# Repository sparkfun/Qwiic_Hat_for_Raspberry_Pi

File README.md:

SparkFun Qwiic pHAT v2.0 for Raspberry Pi
========================================

[*SparkFun Qwiic pHAT for Raspberry Pi*](https://www.sparkfun.com/products/15945)

This is a board that connects the I<sup>2</sup>C bus on the Raspberry Pi to 4 Qwiic connectors.

Repository Contents
-------------------

* **/Hardware** - Eagle design files (.brd, .sch)
* **/Production** - Production panel files (.brd)

Documentation
--------------
* **[Hookup Guide](https://learn.sparkfun.com/tutorials/qwiic-phat-for-raspberry-pi-hookup-guide)** - Basic hookup guide for the SparkFun Qwiic pHAT for Raspberry Pi.

Product Versions
----------------
* [DEV-15945](https://www.sparkfun.com/products/15945)- Qwiic pHAT v2.0
* [DEV-15351](https://www.sparkfun.com/products/15351)- Qwiic pHAT v1.0
* [DEV-14459](https://www.sparkfun.com/products/14459) - Qwiic HAT SparkFun Reds Initial Release
* [DEV-14292](https://www.sparkfun.com/products/14292) - SparkX Version

License Information
-------------------

This product is _**open source**_! 

Please review the LICENSE.md file for license information. 

If you have any questions or concerns on licensing, please contact technical support on our [SparkFun forums](https://forum.sparkfun.com/viewforum.php?f=152).

Distributed as-is; no warranty is given.

- Your friends at SparkFun.

_<COLLABORATION CREDIT>_

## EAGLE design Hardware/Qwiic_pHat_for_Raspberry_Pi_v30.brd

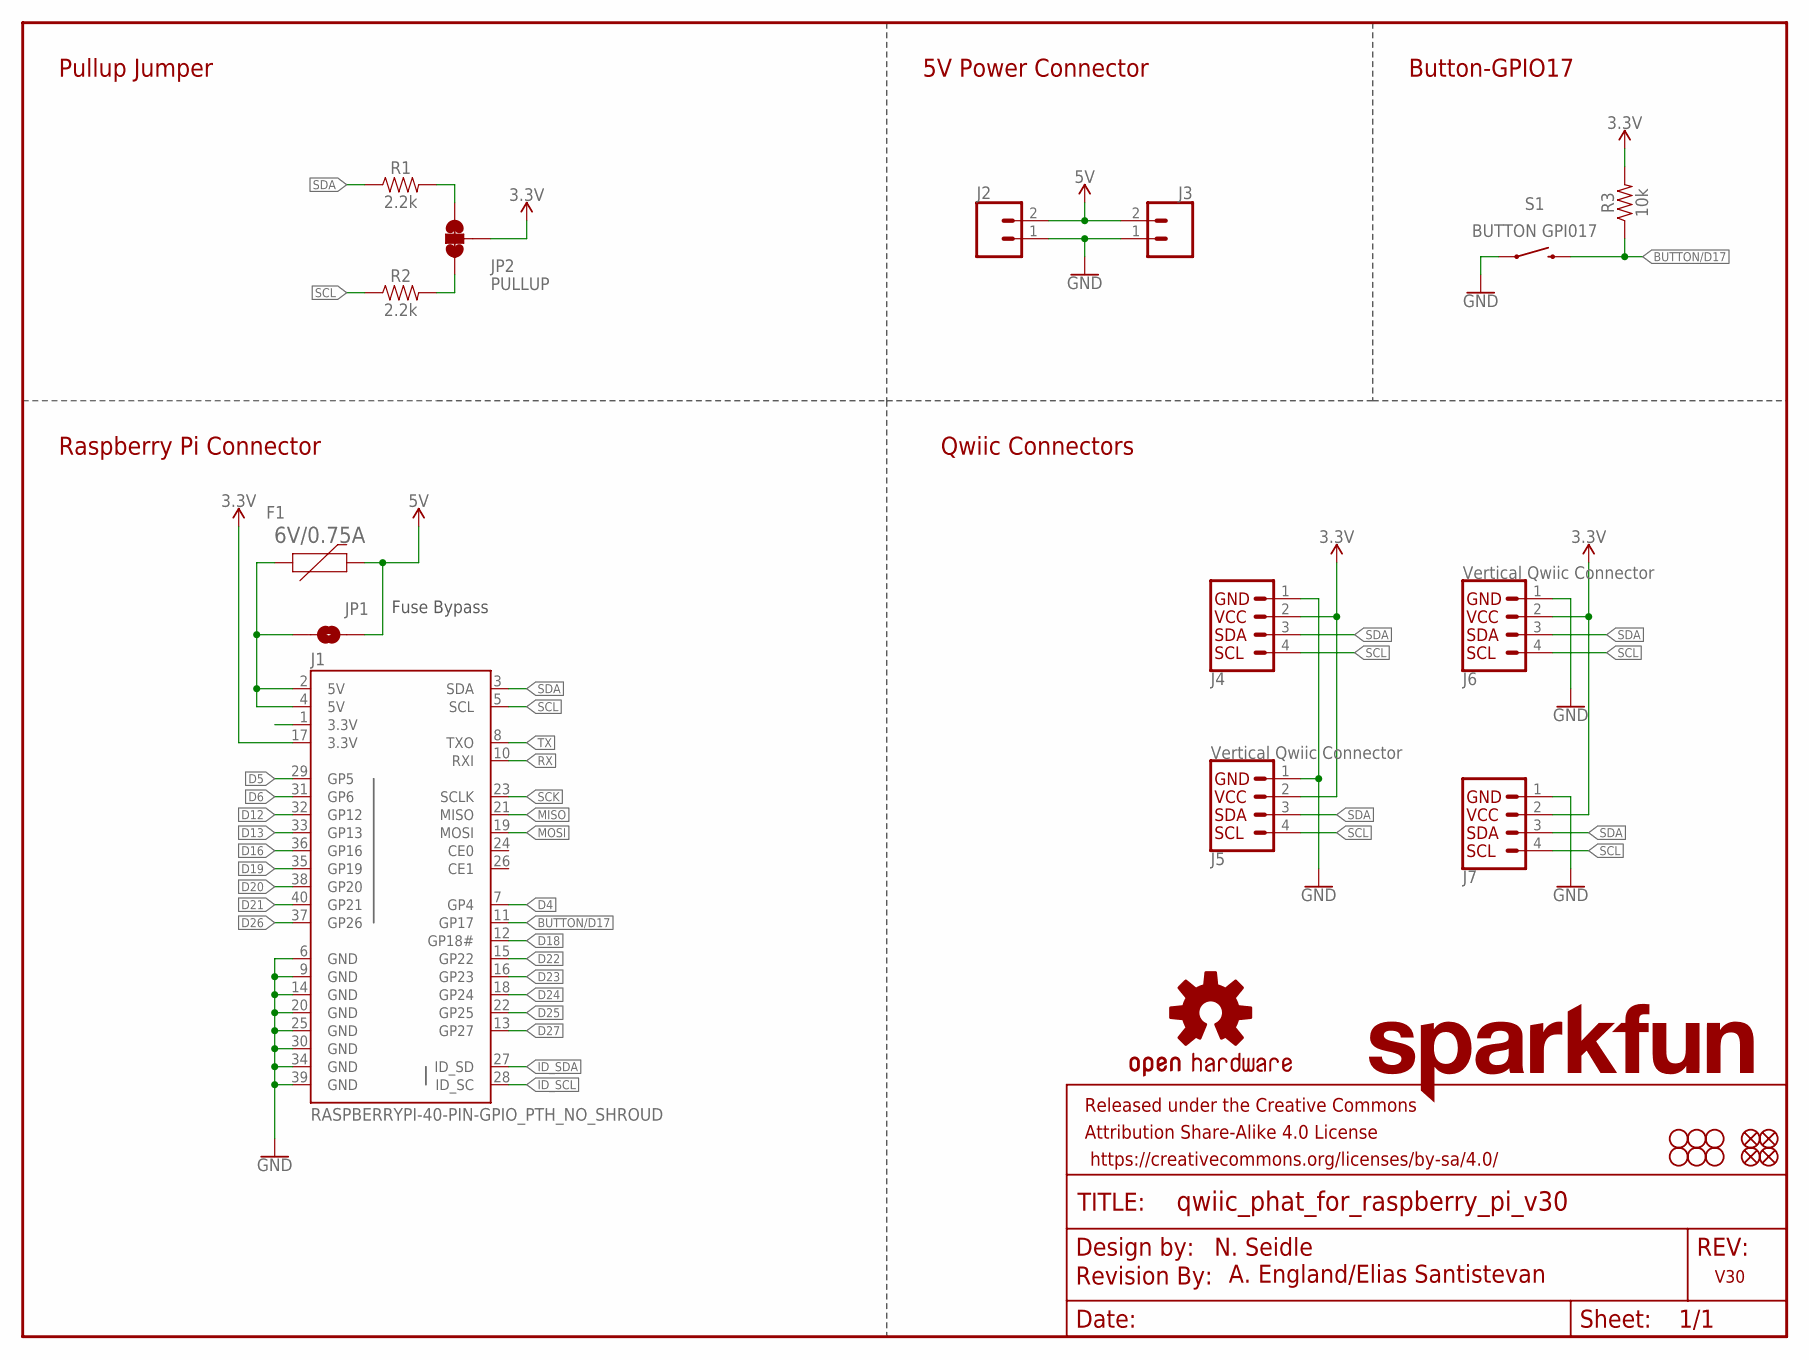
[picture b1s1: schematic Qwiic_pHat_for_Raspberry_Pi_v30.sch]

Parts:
F1: 6V/0.75A; 1206
FD1, FD2, FD3, FD4: FIDUCIAL1X2; FIDUCIAL-1X2
FRAME1: FRAME-LETTER; CREATIVE_COMMONS
H1, H2, H3, H4, H5, H6: STAND-OFFTIGHT; STAND-OFF-TIGHT
J1: RASPBERRYPI-40-PIN-GPIO_PTH_NO_SHROUD; 2X20
J2: CONN_023.5MM-NO_SILK; SCREWTERMINAL-3.5MM-2-NS
J3: CONN_023.5MM; SCREWTERMINAL-3.5MM-2
J4, J7: Qwiic Right Angle; JST04_1MM_RA
J5, J6: Vertical Qwiic Connector; JST04_1MM_VERT
JP1: JUMPER-SMT_2_NO_SILK; SMT-JUMPER_2_NO_SILK
JP2: PULLUP; SMT-JUMPER_3_2-NC_TRACE_NO-SILK
LOGO1: REVISION
LOGO2: OSHW-LOGOS; OSHW-LOGO-S
LOGO3: SFE_LOGO_NAME.1_INCH; SFE_LOGO_NAME_.1
R1, R2: 2.2k; 0603
R3: 10k; 0603
S1: BUTTON GPI017; TACTILE_SWITCH_SMD_5.2MM

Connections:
3.3V: J1.17 (3.3V), J4.2, J5.2, J6.2, J7.2, JP2.2, R3.2
5V: F1.2, J2.2, J3.2, JP1.2
BUTTON/D17: J1.11 (GP17), R3.1, S1.3 (2)
D4: J1.7 (GP4)
D5: J1.29 (GP5)
D6: J1.31 (GP6)
D12: J1.32 (GP12)
D13: J1.33 (GP13)
D16: J1.36 (GP16)
D18: J1.12 (GP18#)
D19: J1.35 (GP19)
D20: J1.38 (GP20)
D21: J1.40 (GP21)
D22: J1.15 (GP22)
D23: J1.16 (GP23)
D24: J1.18 (GP24)
D25: J1.22 (GP25)
D26: J1.37 (GP26)
D27: J1.13 (GP27)
GND: J1.6 (GND), J1.9 (GND), J1.14 (GND), J1.20 (GND), J1.25 (GND), J1.30 (GND), J1.34 (GND), J1.39 (GND), J2.1, J3.1, J4.1, J5.1, J6.1, J7.1, S1.1
ID_SCL: J1.28 (ID_SC)
ID_SDA: J1.27 (ID_SD)
MISO: J1.21 (MISO)
MOSI: J1.19 (MOSI)
unnamed: F1.1, J1.2 (5V), J1.4 (5V), JP1.1
unnamed: JP2.3, R1.2
unnamed: JP2.1, R2.2
RX: J1.10 (RXI)
SCK: J1.23 (SCLK)
SCL: J1.5 (SCL), J4.4, J5.4, J6.4, J7.4, R2.1
SDA: J1.3 (SDA), J4.3, J5.3, J6.3, J7.3, R1.1
TX: J1.8 (TXO)

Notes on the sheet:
N. Seidle
Raspberry Pi Connector
V30
Qwiic Connectors
A. England/Elias Santistevan
Pullup Jumper
5V Power Connector
Button-GPIO17
Fuse Bypass

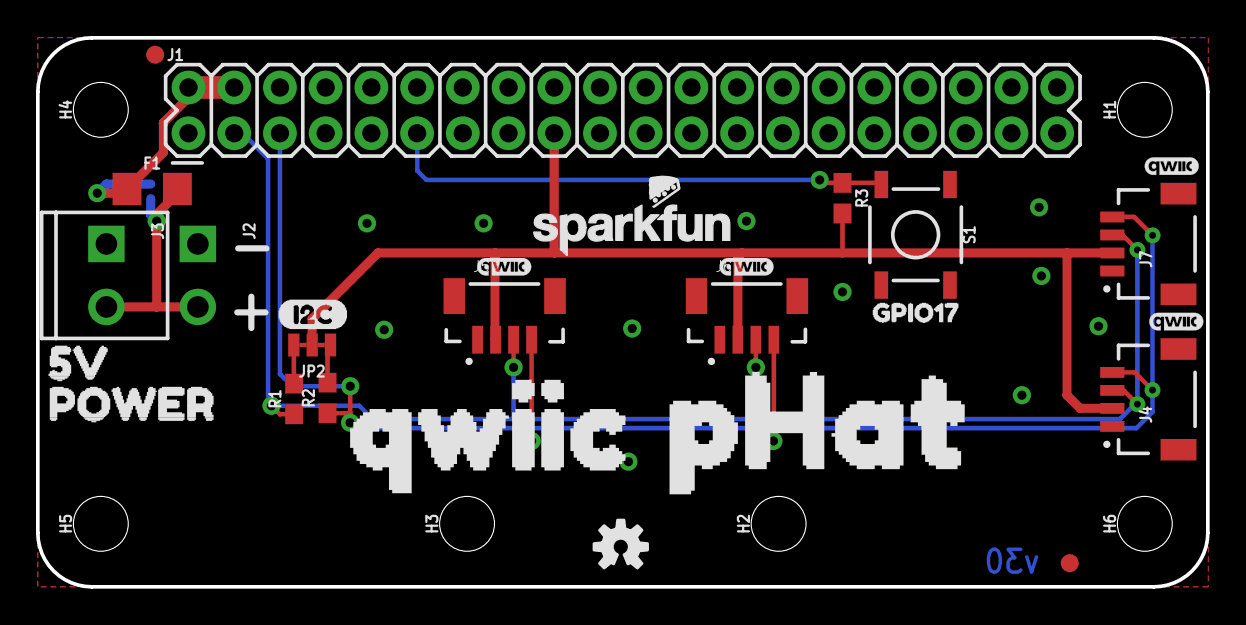
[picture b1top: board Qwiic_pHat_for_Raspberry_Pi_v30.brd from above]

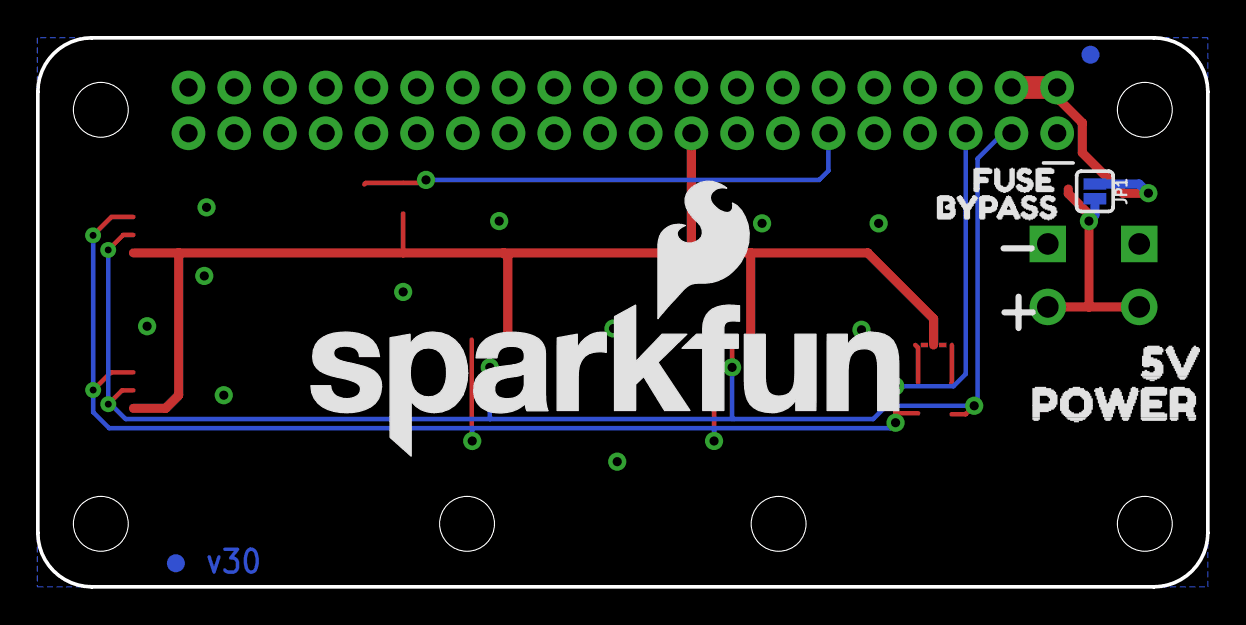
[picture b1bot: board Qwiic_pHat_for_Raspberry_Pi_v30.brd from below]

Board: 2 copper layers, 65.0 x 30.5 mm, 44 parts (8 on the bottom side), 9 nets.

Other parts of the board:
U$1: PIE_1F967#PNG
U$2: I2C-()
U$3: PHAT0
U$6: FUSE0
U$7: BYPASS1
U$8, U$11, U$16, U$17: QWIIC_3MM
U$9: GPIO173
U$10: SFE_LOGO_NAME_FLAME_.3
U$12, U$15: 5V0
U$13, U$14: POWER1
U$18: QWIIC0

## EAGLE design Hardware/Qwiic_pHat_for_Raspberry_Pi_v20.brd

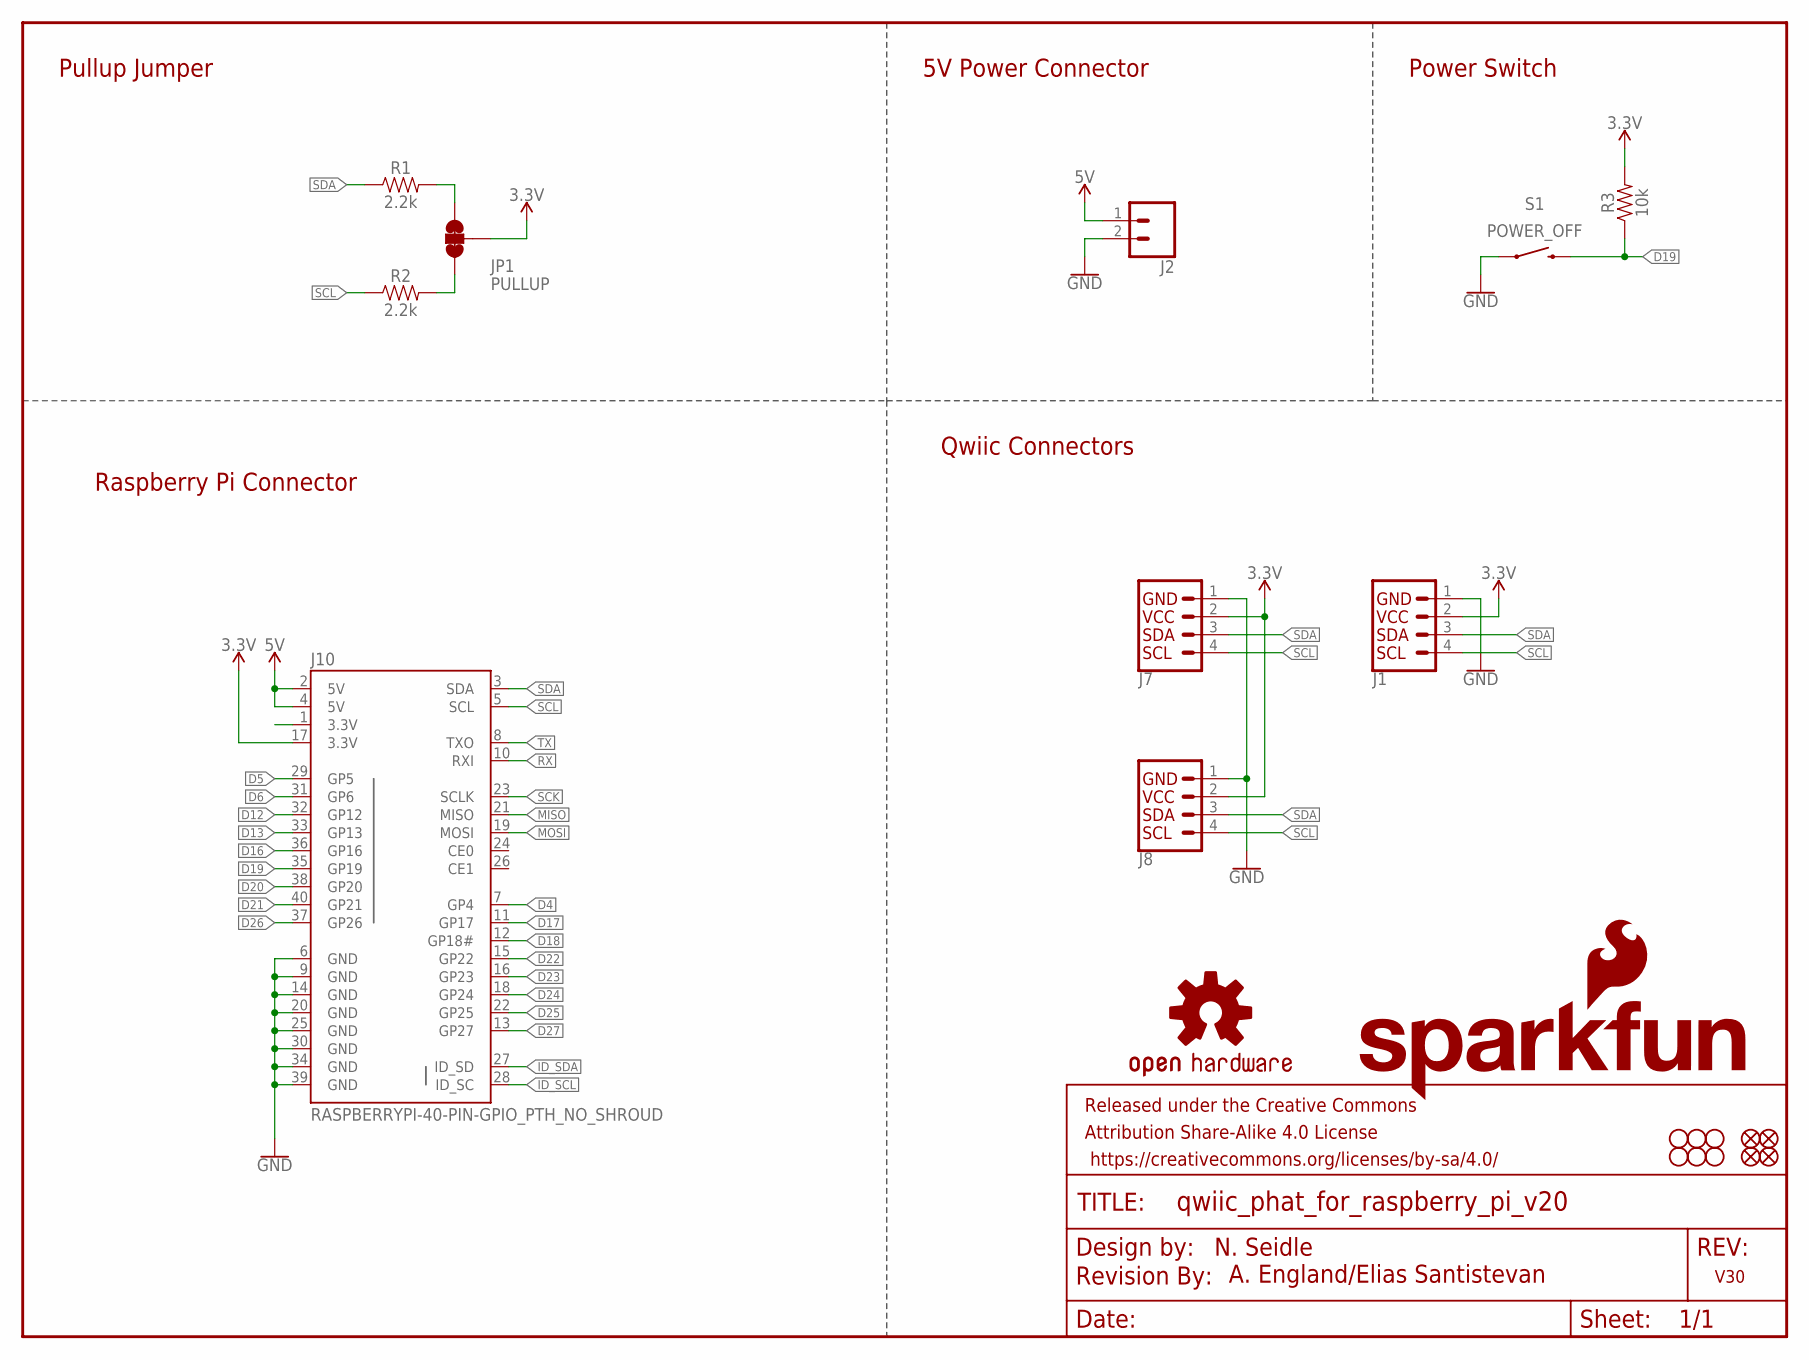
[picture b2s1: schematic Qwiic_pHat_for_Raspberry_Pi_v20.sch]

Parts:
FD1, FD2, FD3, FD4: FIDUCIAL1X2; FIDUCIAL-1X2
FRAME1: FRAME-LETTER; CREATIVE_COMMONS
H1, H2, H3, H4, H5, H6: STAND-OFFTIGHT; STAND-OFF-TIGHT
J1, J7, J8: Qwiic Right Angle; JST04_1MM_RA
J2: CONN_023.5MM-NO_SILK; SCREWTERMINAL-3.5MM-2-NS
J10: RASPBERRYPI-40-PIN-GPIO_PTH_NO_SHROUD; 2X20
JP1: PULLUP; SMT-JUMPER_3_2-NC_TRACE_NO-SILK
LOGO1: SFE_LOGO_NAME_FLAME.2_INCH; SFE_LOGO_NAME_FLAME_.2
LOGO2: REVISION
LOGO3: OSHW-LOGOS; OSHW-LOGO-S
R1, R2: 2.2k; 0603
R3: 10k; 0603
S1: POWER_OFF; TACTILE_SWITCH_SMD_5.2MM

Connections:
3.3V: J1.2, J7.2, J8.2, J10.17 (3.3V), JP1.2, R3.2
5V: J2.1, J10.2 (5V), J10.4 (5V)
D4: J10.7 (GP4)
D5: J10.29 (GP5)
D6: J10.31 (GP6)
D12: J10.32 (GP12)
D13: J10.33 (GP13)
D16: J10.36 (GP16)
D17: J10.11 (GP17)
D18: J10.12 (GP18#)
D19: J10.35 (GP19), R3.1, S1.3 (2)
D20: J10.38 (GP20)
D21: J10.40 (GP21)
D22: J10.15 (GP22)
D23: J10.16 (GP23)
D24: J10.18 (GP24)
D25: J10.22 (GP25)
D26: J10.37 (GP26)
D27: J10.13 (GP27)
GND: J1.1, J2.2, J7.1, J8.1, J10.6 (GND), J10.9 (GND), J10.14 (GND), J10.20 (GND), J10.25 (GND), J10.30 (GND), J10.34 (GND), J10.39 (GND), S1.1
ID_SCL: J10.28 (ID_SC)
ID_SDA: J10.27 (ID_SD)
MISO: J10.21 (MISO)
MOSI: J10.19 (MOSI)
unnamed: JP1.3, R1.2
unnamed: JP1.1, R2.2
RX: J10.10 (RXI)
SCK: J10.23 (SCLK)
SCL: J1.4, J7.4, J8.4, J10.5 (SCL), R2.1
SDA: J1.3, J7.3, J8.3, J10.3 (SDA), R1.1
TX: J10.8 (TXO)

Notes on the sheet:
N. Seidle
Raspberry Pi Connector
V30
Qwiic Connectors
A. England/Elias Santistevan
Pullup Jumper
5V Power Connector
Power Switch

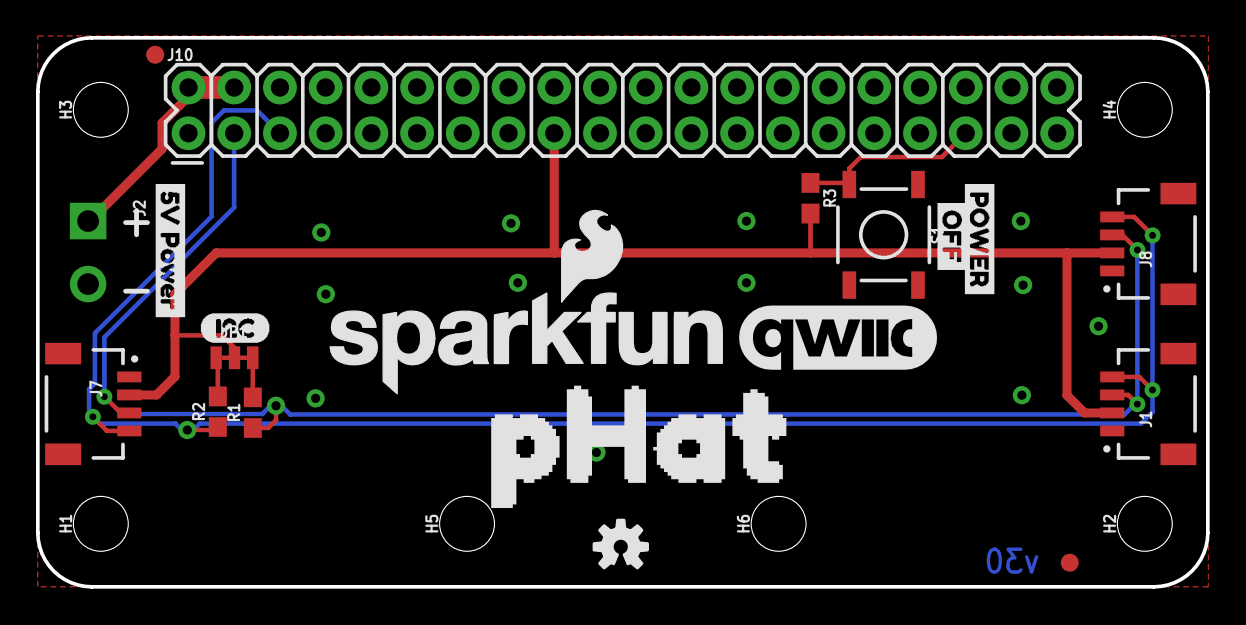
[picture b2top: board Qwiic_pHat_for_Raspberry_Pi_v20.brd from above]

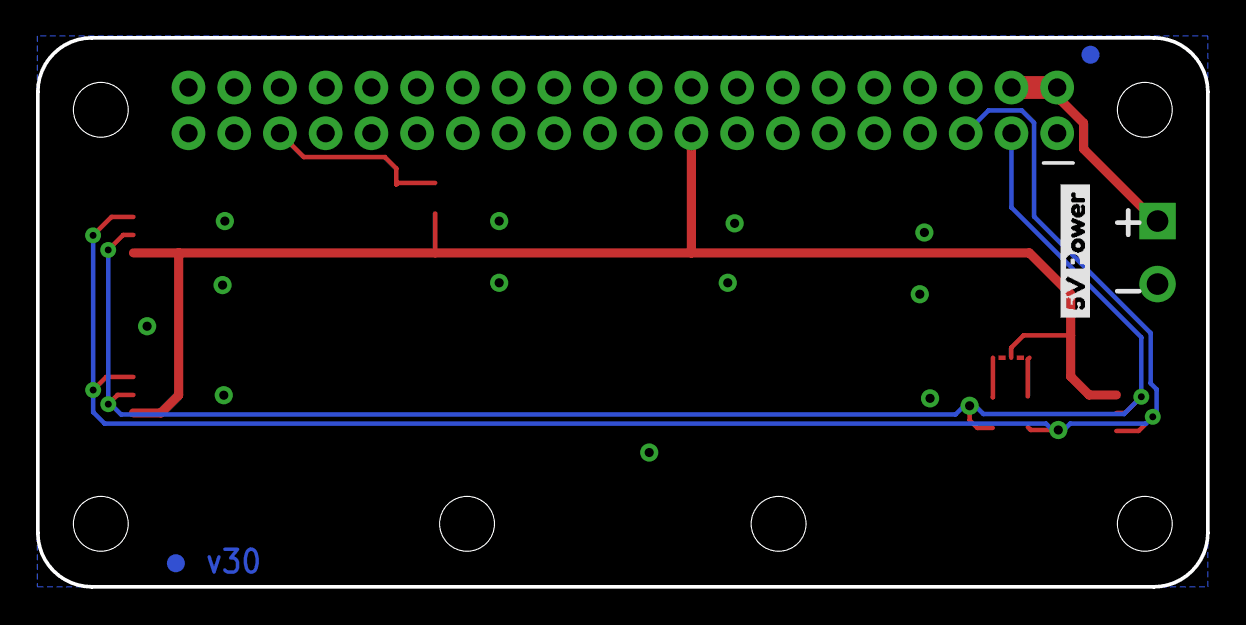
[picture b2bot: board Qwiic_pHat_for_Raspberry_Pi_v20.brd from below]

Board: 2 copper layers, 65.0 x 30.5 mm, 33 parts (3 on the bottom side), 8 nets.

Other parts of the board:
U$1: QWIIC_11MM
U$2: I2C-()
U$3: PHAT0
U$4, U$5: QWIIC_BOARD_MOUNT_NOHOLES
U$6, U$7: 5V_POWER0
U$8: POWER2
U$9: OFF1

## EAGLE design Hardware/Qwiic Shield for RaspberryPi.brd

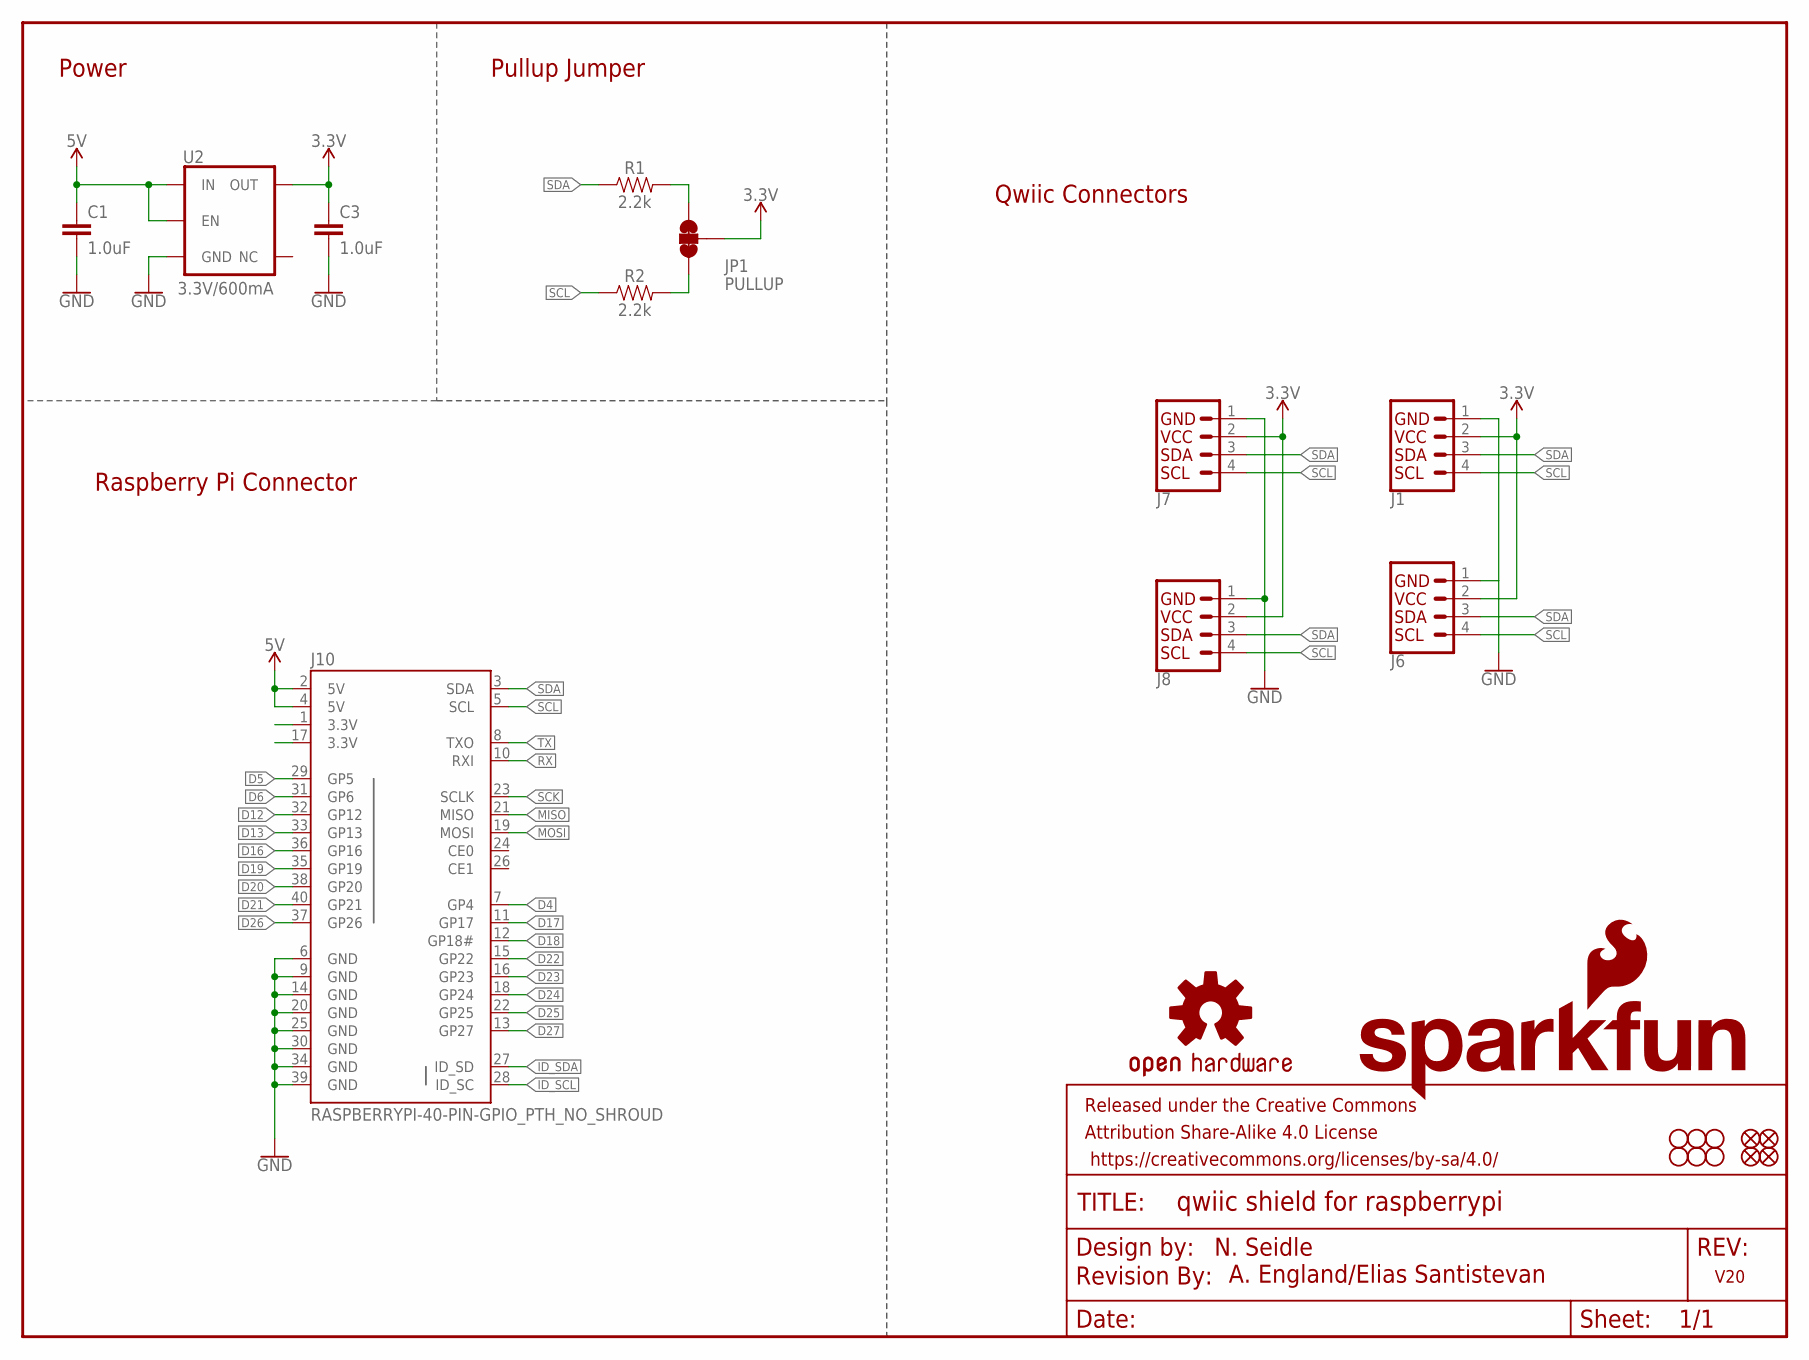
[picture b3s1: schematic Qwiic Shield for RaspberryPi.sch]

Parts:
C1, C3: 1.0uF; 0603
FD1, FD2, FD3, FD4: FIDUCIAL1X2; FIDUCIAL-1X2
FRAME1: FRAME-LETTER; CREATIVE_COMMONS
H1, H2, H3, H4, H5, H6: STAND-OFFTIGHT; STAND-OFF-TIGHT
J1, J6, J7, J8: Qwiic Right Angle; JST04_1MM_RA
J10: RASPBERRYPI-40-PIN-GPIO_PTH_NO_SHROUD; 2X20
JP1: PULLUP; SMT-JUMPER_3_2-NC_TRACE_NO-SILK
LOGO1: SFE_LOGO_NAME_FLAME.2_INCH; SFE_LOGO_NAME_FLAME_.2
LOGO2: REVISION
LOGO3: OSHW-LOGOS; OSHW-LOGO-S
R1, R2: 2.2k; 0603
U2: 3.3V/600mA; SOT23-5

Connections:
3.3V: C3.1, J1.2, J6.2, J7.2, J8.2, JP1.2, U2.5 (OUT)
5V: C1.1, J10.2 (5V), J10.4 (5V), U2.1 (IN), U2.3 (EN)
D4: J10.7 (GP4)
D5: J10.29 (GP5)
D6: J10.31 (GP6)
D12: J10.32 (GP12)
D13: J10.33 (GP13)
D16: J10.36 (GP16)
D17: J10.11 (GP17)
D18: J10.12 (GP18#)
D19: J10.35 (GP19)
D20: J10.38 (GP20)
D21: J10.40 (GP21)
D22: J10.15 (GP22)
D23: J10.16 (GP23)
D24: J10.18 (GP24)
D25: J10.22 (GP25)
D26: J10.37 (GP26)
D27: J10.13 (GP27)
GND: C1.2, C3.2, J1.1, J6.1, J7.1, J8.1, J10.6 (GND), J10.9 (GND), J10.14 (GND), J10.20 (GND), J10.25 (GND), J10.30 (GND), J10.34 (GND), J10.39 (GND), U2.2 (GND)
ID_SCL: J10.28 (ID_SC)
ID_SDA: J10.27 (ID_SD)
MISO: J10.21 (MISO)
MOSI: J10.19 (MOSI)
unnamed: JP1.3, R1.2
unnamed: JP1.1, R2.2
RX: J10.10 (RXI)
SCK: J10.23 (SCLK)
SCL: J1.4, J6.4, J7.4, J8.4, J10.5 (SCL), R2.1
SDA: J1.3, J6.3, J7.3, J8.3, J10.3 (SDA), R1.1
TX: J10.8 (TXO)

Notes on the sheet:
N. Seidle
Raspberry Pi Connector
V20
Qwiic Connectors
Power
A. England/Elias Santistevan
Pullup Jumper

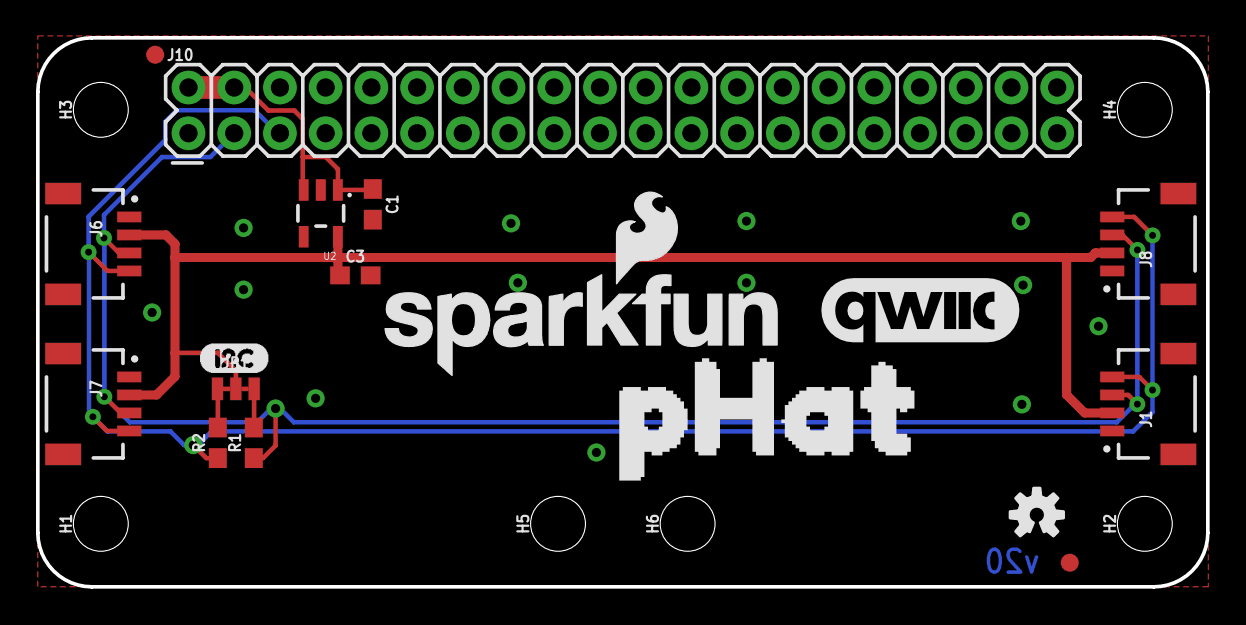
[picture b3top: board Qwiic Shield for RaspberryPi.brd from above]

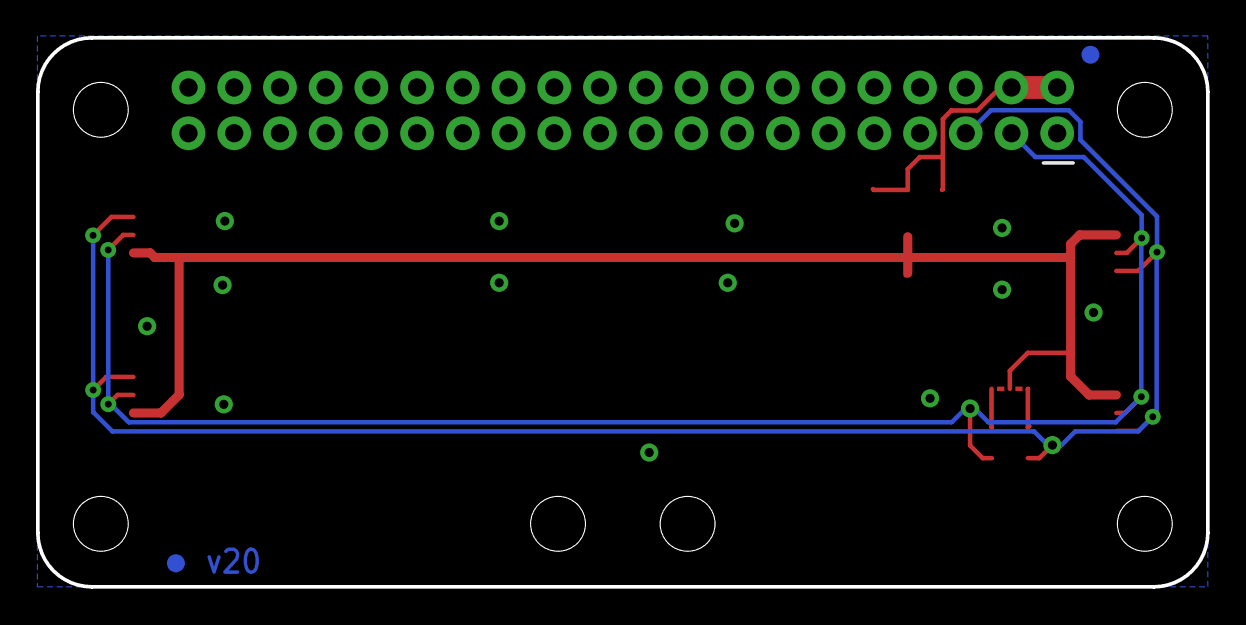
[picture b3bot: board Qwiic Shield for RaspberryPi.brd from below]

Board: 2 copper layers, 65.0 x 30.5 mm, 28 parts (2 on the bottom side), 7 nets.

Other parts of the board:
U$1: QWIIC_11MM
U$2: I2C-()
U$3: PHAT0

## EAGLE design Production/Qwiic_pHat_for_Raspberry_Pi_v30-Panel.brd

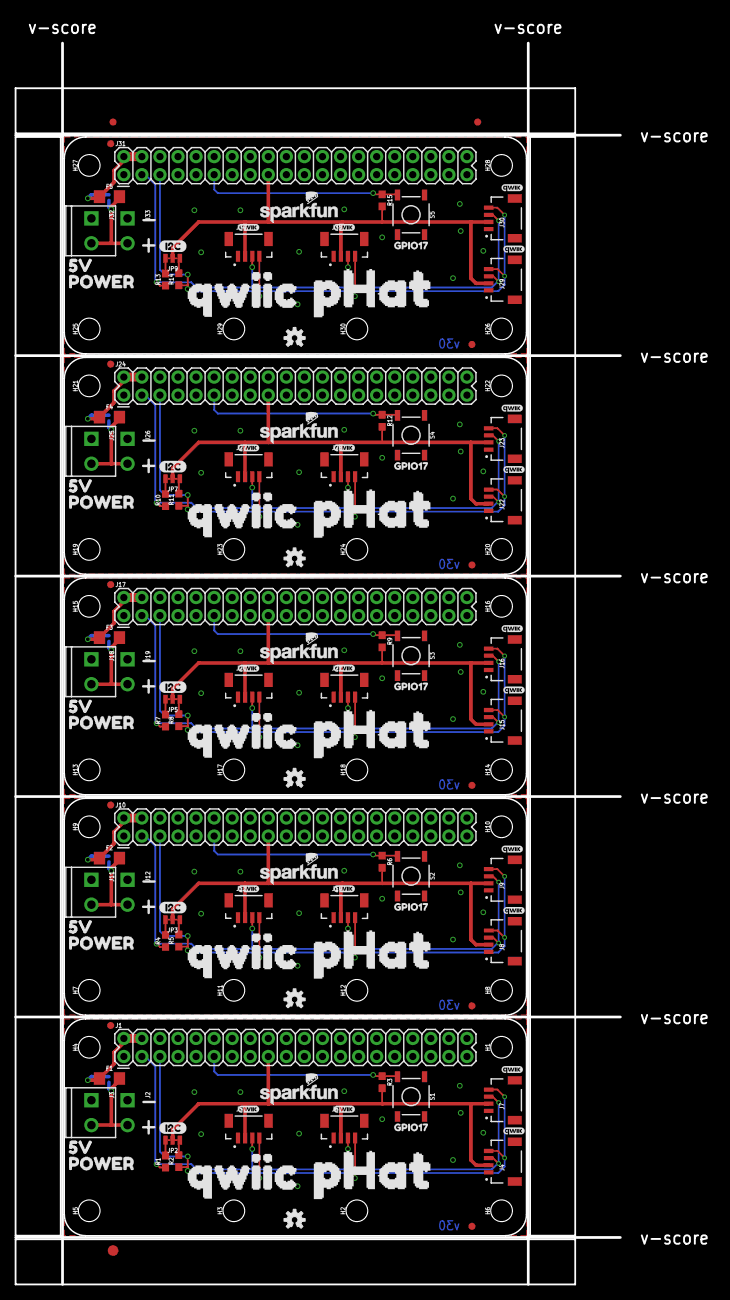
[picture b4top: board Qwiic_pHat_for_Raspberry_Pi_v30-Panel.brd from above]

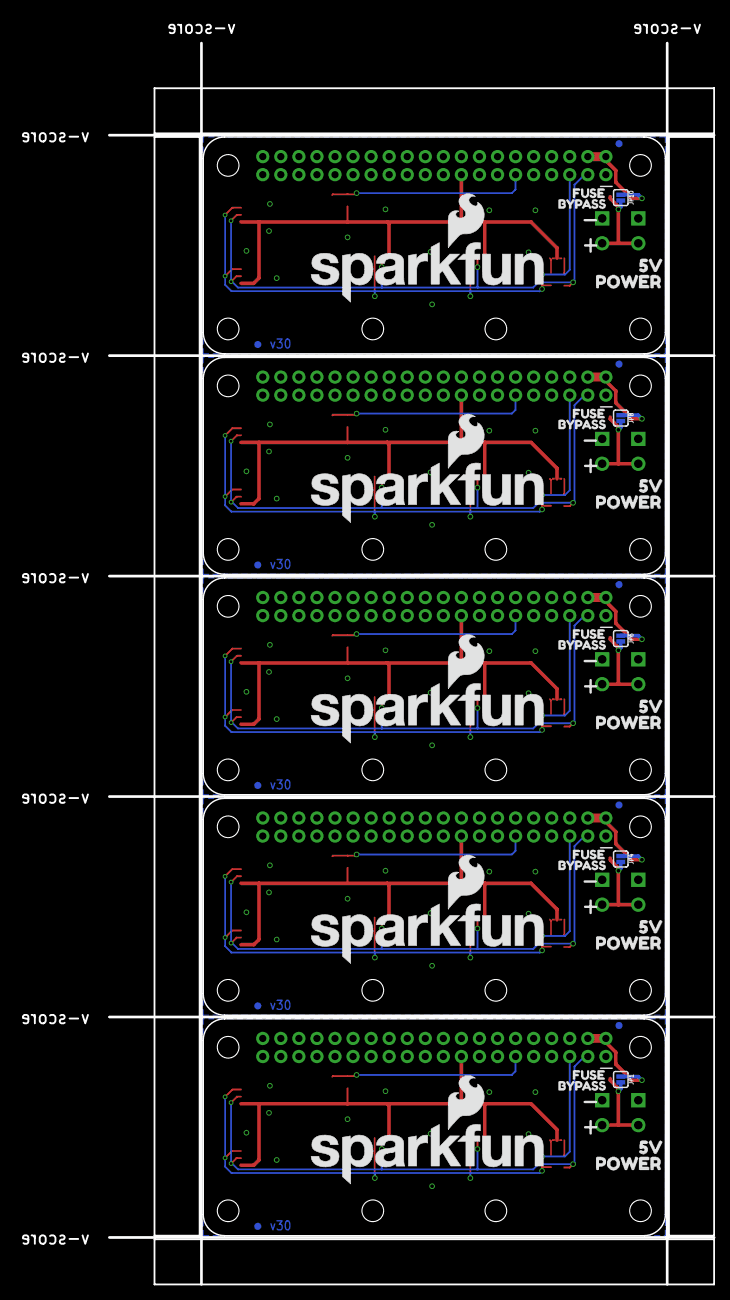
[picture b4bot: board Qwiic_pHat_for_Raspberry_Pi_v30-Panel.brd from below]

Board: 2 copper layers, 98.3 x 178.5 mm, 223 parts (40 on the bottom side), 45 nets.

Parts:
E$1, E$2: FIDUCIAL-1X2
E$3: FIDUCIAL-1.5X3
F1, F2, F3, F4, F5: 6V/0.75A; 1206
FD1, FD2, FD3, FD4, FD5, FD6, FD7, FD8, FD9, FD10, FD11, FD12, FD13, FD14, FD15, FD16, FD17, FD18, FD19, FD20: FIDUCIAL1X2; FIDUCIAL-1X2
FRAME1, FRAME2, FRAME3, FRAME4, FRAME5: FRAME-LETTER; CREATIVE_COMMONS
H1, H2, H3, H4, H5, H6, H7, H8, H9, H10, H11, H12, H13, H14, H15, H16, H17, H18, H19, H20, H21, H22, H23, H24, H25, H26, H27, H28, H29, H30: STAND-OFFTIGHT; STAND-OFF-TIGHT
J1, J10, J17, J24, J31: RASPBERRYPI-40-PIN-GPIO_PTH_NO_SHROUD; 2X20
J2, J12, J19, J26, J33: SCREWTERMINAL-3.5MM-2-NS
J3, J11, J18, J25, J32: SCREWTERMINAL-3.5MM-2
J4, J7, J8, J9, J15, J16, J22, J23, J29, J30: Qwiic Right Angle; JST04_1MM_RA
J5, J6, J13, J14, J20, J21, J27, J28, J34, J35: Vertical Qwiic Connector; JST04_1MM_VERT
JP1, JP4, JP6, JP8, JP10: JUMPER-SMT_2_NO_SILK; SMT-JUMPER_2_NO_SILK
JP2, JP3, JP5, JP7, JP9: PULLUP; SMT-JUMPER_3_2-NC_TRACE_NO-SILK
LOGO1, LOGO4, LOGO7, LOGO10, LOGO13: REVISION
LOGO2, LOGO5, LOGO8, LOGO11, LOGO14: OSHW-LOGOS; OSHW-LOGO-S
LOGO3, LOGO6, LOGO9, LOGO12, LOGO15: SFE_LOGO_NAME.1_INCH; SFE_LOGO_NAME_.1
R1, R2, R4, R5, R7, R8, R10, R11, R13, R14: 2.2k; 0603
R3, R6, R9, R12, R15: 10k; 0603
S1, S2, S3, S4, S5: BUTTON GPI017; TACTILE_SWITCH_SMD_5.2MM
U$1, U$31, U$47, U$63, U$79: PIE_1F967#PNG
U$2, U$5, U$34, U$50, U$66: I2C-()
U$3, U$4, U$33, U$49, U$65: PHAT0
U$6, U$20, U$36, U$52, U$68: FUSE0
U$7, U$21, U$37, U$53, U$69: BYPASS1
U$8, U$11, U$16, U$17, U$22, U$27, U$28, U$29, U$38, U$43, U$44, U$45, U$54, U$59, U$60, U$61, U$70, U$75, U$76, U$77: QWIIC_3MM
U$9, U$19, U$35, U$51, U$67: GPIO173
U$10, U$32, U$48, U$64, U$80: SFE_LOGO_NAME_FLAME_.3
U$12, U$15, U$23, U$26, U$39, U$42, U$55, U$58, U$71, U$74: 5V0
U$13, U$14, U$24, U$25, U$40, U$41, U$56, U$57, U$72, U$73: POWER1
U$18, U$30, U$46, U$62, U$78: QWIIC0

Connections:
3.3V: J1.17, J4.2, J5.2, J6.2, J7.2, JP2.2, R3.2
3.3V1: J8.2, J9.2, J10.17, J13.2, J14.2, JP3.2, R6.2
3.3V2: J15.2, J16.2, J17.17, J20.2, J21.2, JP5.2, R9.2
3.3V3: J22.2, J23.2, J24.17, J27.2, J28.2, JP7.2, R12.2
3.3V4: J29.2, J30.2, J31.17, J34.2, J35.2, JP9.2, R15.2
5V: F1.2, J2.2, J3.2, JP1.2
5V1: F2.2, J11.2, J12.2, JP4.2
5V2: F3.2, J18.2, J19.2, JP6.2
5V3: F4.2, J25.2, J26.2, JP8.2
5V4: F5.2, J32.2, J33.2, JP10.2
BUTTON/D1: J10.11, R6.1, S2.3
BUTTON/D2: J17.11, R9.1, S3.3
BUTTON/D3: J24.11, R12.1, S4.3
BUTTON/D4: J31.11, R15.1, S5.3
BUTTON/D17: J1.11, R3.1, S1.3
GND: J1.6, J1.9, J1.14, J1.20, J1.25, J1.30, J1.34, J1.39, J2.1, J3.1, J4.1, J5.1, J6.1, J7.1, S1.1
GND1: J8.1, J9.1, J10.6, J10.9, J10.14, J10.20, J10.25, J10.30, J10.34, J10.39, J11.1, J12.1, J13.1, J14.1, S2.1
GND2: J15.1, J16.1, J17.6, J17.9, J17.14, J17.20, J17.25, J17.30, J17.34, J17.39, J18.1, J19.1, J20.1, J21.1, S3.1
GND3: J22.1, J23.1, J24.6, J24.9, J24.14, J24.20, J24.25, J24.30, J24.34, J24.39, J25.1, J26.1, J27.1, J28.1, S4.1
GND4: J29.1, J30.1, J31.6, J31.9, J31.14, J31.20, J31.25, J31.30, J31.34, J31.39, J32.1, J33.1, J34.1, J35.1, S5.1
unnamed: F1.1, J1.2, J1.4, JP1.1
unnamed: JP2.3, R1.2
unnamed: JP2.1, R2.2
unnamed: JP3.3, R4.2
unnamed: JP3.1, R5.2
unnamed: F2.1, J10.2, J10.4, JP4.1
unnamed: JP5.3, R7.2
unnamed: JP5.1, R8.2
unnamed: F3.1, J17.2, J17.4, JP6.1
unnamed: JP7.3, R10.2
unnamed: JP7.1, R11.2
unnamed: F4.1, J24.2, J24.4, JP8.1
unnamed: JP9.3, R13.2
unnamed: JP9.1, R14.2
unnamed: F5.1, J31.2, J31.4, JP10.1
SCL: J1.5, J4.4, J5.4, J6.4, J7.4, R2.1
SCL1: J8.4, J9.4, J10.5, J13.4, J14.4, R5.1
SCL2: J15.4, J16.4, J17.5, J20.4, J21.4, R8.1
SCL3: J22.4, J23.4, J24.5, J27.4, J28.4, R11.1
SCL4: J29.4, J30.4, J31.5, J34.4, J35.4, R14.1
SDA: J1.3, J4.3, J5.3, J6.3, J7.3, R1.1
SDA1: J8.3, J9.3, J10.3, J13.3, J14.3, R4.1
SDA2: J15.3, J16.3, J17.3, J20.3, J21.3, R7.1
SDA3: J22.3, J23.3, J24.3, J27.3, J28.3, R10.1
SDA4: J29.3, J30.3, J31.3, J34.3, J35.3, R13.1

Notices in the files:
parts and their libraries:
SparkFun-Aesthetics: Licensing: CC v3.0 Share-Alike You are welcome to use this library for commercial purposes.
SparkFun-Aesthetics: Released under the Creative Commons Attribution Share-Alike 4.0 License
SparkFun-Aesthetics: https://creativecommons.org/licenses/by-sa/4.0
